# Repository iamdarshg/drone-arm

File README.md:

This is a codebase that is woring to create a hardware+software solution for dron control and management in a relatively modular manner. 
This is a codebase that is woring to create a hardware+software solution for dron control and management in a relatively modular manner.
This needs to be inherenly zero-trust, zero-fail and easy to analyse statically. The langauge of choice is C, with rust and python tooling accepted as well.Follow the 10 rules as set by nasa for code, the same should apply here due to the similar no-fail environment.
Currently, the main control board has been designed and the auxiallry field-oriented control esc needs to be designed.
Ideally, as much of this code as possible should be library free and written entirely from scratch. If any libraries are used beyond standard c libararies, they should all be stored within this folder, nowehere else.
Please add as much documentation as is needed, whenevr you refer to something just download and leave it in the docs folder. Please use the pico SDK exclusively as a library for C and/or write everything using reigster level functions.
Build will occur via Meson & Ninja. This means we will be compiling the whole thing using the arm toolchain, against the headers and flash tables and such from the SDK.
When debug is enabled in the meson build, we will output the assembly instead of the .uf2 file.

## Motor Platform (selected prototype baseline)

The ESC (Rev-B) is being optimized for the **Flycci FA4119 KV350** ([product page](https://robu.in/product/flycci-fpv-brushless-motors-fa4119-350kv/)). The current prototype decision, alternatives, cost model, proposed 550 Kv rewind, selected 8x4.5 propeller and mandatory validation gates are documented in [hardware/motor_release/FA4119_PROPULSION_DECISION.md](hardware/motor_release/FA4119_PROPULSION_DECISION.md).

- 12N14P outrunner (**7 pole pairs**), stator 41x19 mm, 280 g w/ cable
- Recommended 10S-12S LiPo, 13" prop, 80 A ESC class
- Measured (12S, HQ13x9-3 3-blade): 8.18 kg max thrust / 3.47 kW max @ 48 V, 74 A battery
- A rewind to **approximately 550 kV** is the experimental target if stock-motor dyno results justify it. The chosen Orange HD 8045 propeller has no verified manufacturer RPM rating in the repository, so the 550 Kv/12S combination requires closed-loop RPM limiting and guarded testing; it is not flight-released.

### eRPM headroom

eRPM = mech RPM x pole pairs (7). At 12S max (50.4 V):

| Winding | No-load RPM | No-load eRPM | Published or initially governed loaded eRPM |
|---|---|---|---|
| 350 kV (stock) | 17,640 | ~123 k | ~77-80 k with the manufacturer's 13-inch test prop |
| 550 kV (rewind) | 27,720 | ~194 k | initially <=91 k with the 8-inch prop (13,000 mechanical-rpm ceiling) |

**280 k eRPM check:** 280 k eRPM = 4.67 kHz electrical = 40,000 mechanical RPM at 7 pole pairs. This remains a possible future bare-rotor research point, not a propeller operating point. An 8-inch prop at 40,000 RPM has approximately 426 m/s rotational tip speed before pitch velocity and is unsuitable. The proposed 550 Kv winding reaches 194 k eRPM at fully charged 12S; initial propeller testing is capped at 13,000 mechanical RPM (91 k eRPM) pending a verified rating for the exact propeller.

## Build Instructions

This project uses Meson and Ninja for building.

### Prerequisites
- [ARM GNU Toolchain](https://developer.arm.com/Tools%20and%20Software/GNU%20Toolchain) (`arm-none-eabi-gcc`)
- [Meson](https://mesonbuild.com/)
- [Ninja](https://ninja-build.com/)
- Python 3

### Configuration
Create a build directory and configure the project:
```bash
meson setup build
```

To enable **Debug Mode** (includes assembly output and `-O0`):
```bash
meson setup build -Ddebug=enabled 
```

### Building
The documented firmware targets are currently blocked: the tracked checkout is
missing source and include paths required by `meson.build`, and the ARM GNU
cross compiler is not available in the build environment. Do not treat this
checkout as producing flight or ESC firmware. See the
[Issue #22 source and build audit](docs/engineering/FIRMWARE_SOURCE_AUDIT.md)
for the reproducible audit commands and recorded failures.

When the required source and toolchain are restored, the intended build command
is:
```bash
ninja -C build
```

### Testing
To build and run the unit tests:
```bash
meson test -C build
```
Current tests include:
- `test_main`: Scheduler and basic async operations.
- `test_clock_safety`: (New) Integrity protection for global clock state.
The main software will run as two non-synchronised loops- the sensor loop and the PWM loop. The one loop will run at the speed of the ESCs and will provide the best estimate for what the thrust should be at any given time to the ESCs, 60Hz if communicating via PWM and 1 kHz if communicating via SPI. This rate will be configurable. This loop may also be offloaded to the PIO modules in the future. The other loop is reponsible for sensor measuerment and fusion.

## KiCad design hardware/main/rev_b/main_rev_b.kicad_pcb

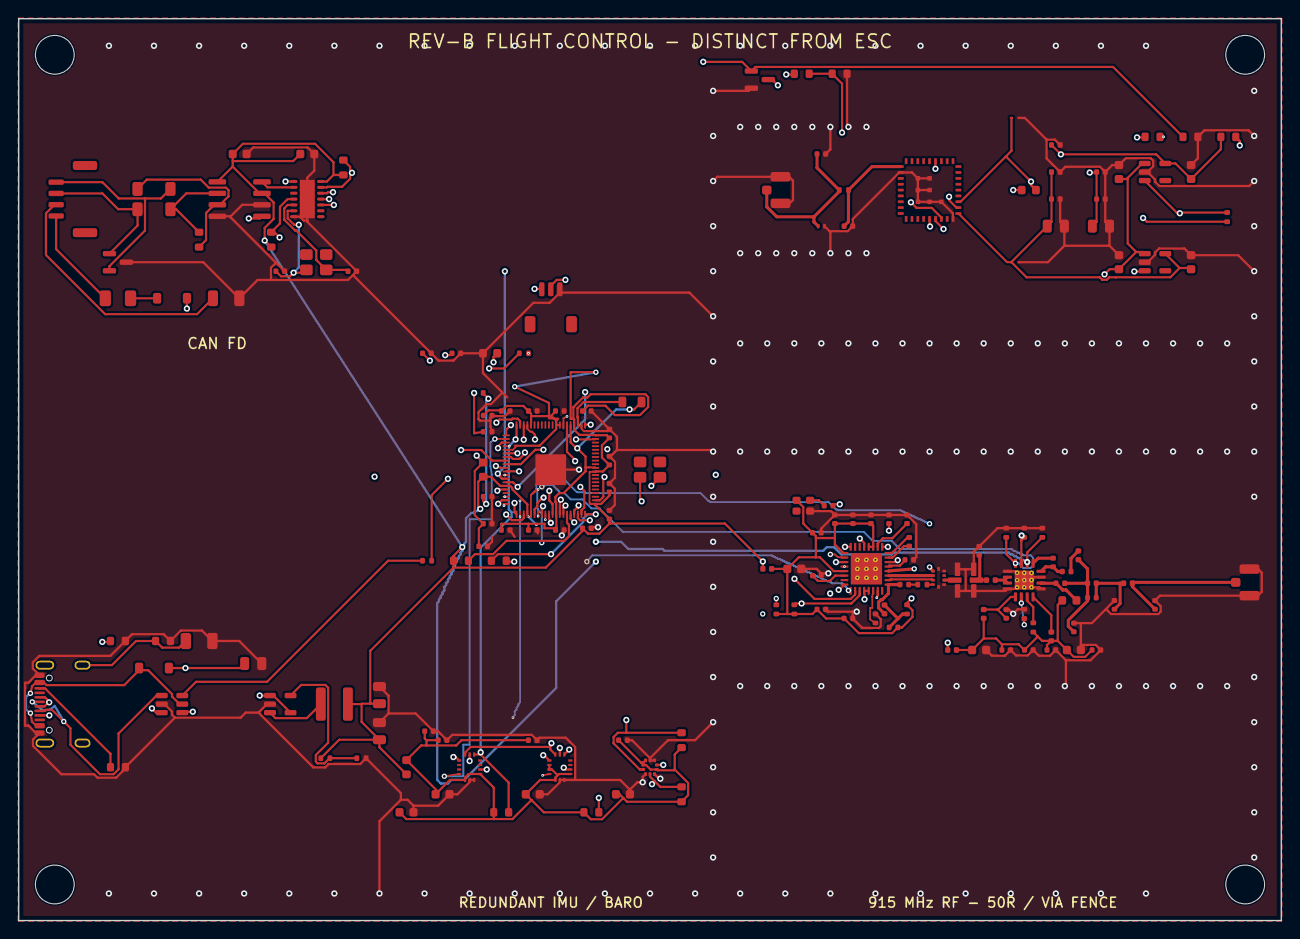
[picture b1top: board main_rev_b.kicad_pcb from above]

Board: 4 copper layers, 140.0 x 100.0 mm, 165 parts (0 on the bottom side), 111 nets.

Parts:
C1: 4.7u 10V; C_0805_2012Metric
C2, C6: 10u 10V; C_0805_2012Metric
C3, C4, C7, C8, C114: 1u; C_0603_1608Metric
C5: 4.7n 2kV; C_1206_3216Metric
C10, C11, C12, C13: 4.7u; C_0402_1005Metric
C20, C21, C86, C89, C120, C121: 15p C0G; C_0402_1005Metric
C30, C31, C32, C33, C34, C35, C36, C37, C38, C39, C40, C41, C42, C50, C52, C54, C56, C71, C75, C101, C115: 100n; C_0402_1005Metric
C51, C53, C55, C57, C100: 2.2u; C_0603_1608Metric
C70: 10u; C_0805_2012Metric
C72, C76, C85: 33p C0G; C_0402_1005Metric
C73: 1u; C_0402_1005Metric
C74: 4.7u; C_0805_2012Metric
C77, C78: DNP; C_0402_1005Metric
C80: 220n; C_0402_1005Metric
C81, C105: 10n; C_0402_1005Metric
C82, C83, C102, C103, C104: 47n; C_0402_1005Metric
C84: 22p C0G; C_0402_1005Metric
C87: 1.8n U2J; C_0402_1005Metric
C88: 0.8p C0G; C_0402_1005Metric
C90: 47p C0G; C_0402_1005Metric
C91: 3.3p C0G; C_0402_1005Metric
C92, C93: 12p C0G; C_0402_1005Metric
C94: 2.4p DNP; C_0402_1005Metric
C95: 7.5p C0G; C_0402_1005Metric
C96: 2.7p DNP; C_0402_1005Metric
C106: 100p; C_0402_1005Metric
C110: 10u; C_0603_1608Metric
C111: 27p; C_0402_1005Metric
C112: 47p; C_0402_1005Metric
C113: 1n; C_0402_1005Metric
C122, C123: 100n; C_0603_1608Metric
D1, D2: PMEG2010ER; D_SOD-123
D10: GREEN; LED_0603_1608Metric
D30: TPD1E0B04DPYR; Texas_DPY0002A_0.6x1mm_P0.65mm
D31, D32: ESD9B3.3ST5G; D_SOD-923
D50: PESD2CANFD24L-T; SOT-23
F1: PTC 0.75A; Fuse_1206_3216Metric
FB1, FB20, FB30: 600R@100MHz; L_0603_1608Metric
FL40: LFD21868MMF1D386
FL41: B39921B3588U410; RF_Filter_4Port
FL50: ACT45B-110-2P-TL003; L_CommonModeChoke_Coilank_ACM4532
H1, H2, H3, H4: M4; MountingHole_4.3mm_M4
J1: USB-C USB2; USB_C_Receptacle_GCT_USB4105-xx-A_16P_TopMnt_Horizontal
J2: ESC_CAN_POWER; JST_GH_SM04B-GHS-TB_1x04-1MP_P1.25mm_Horizontal
J10: SWD; JST_SH_SM03B-SRSS-TB_1x03-1MP_P1.00mm_Horizontal
J30: GNSS_UFL; U.FL_Hirose_U.FL-R-SMT-1_Vertical
J40: 915MHz_ANT; U.FL_Hirose_U.FL-R-SMT-1_Vertical
L1: 3.3u AOTA-B201610S3R3-101-T; L_0805_2012Metric
L2: 2.2u 3.5A; L_APV_ANR4018
L40: 1k@100MHz; L_0402_1005Metric
L41: 8.2n; L_0402_1005Metric
L42, L45: 10n; L_0402_1005Metric
L43: 1.5n; L_0402_1005Metric
L44: 15n; L_0402_1005Metric
L46: 22n; L_0603_1608Metric
L47: 7.5n; L_0402_1005Metric
L48: 2.9n; L_0402_1005Metric
L49: 9.1n; L_0402_1005Metric
Q30: 2N7002; SOT-23
R1, R2: 5.1k; R_0603_1608Metric
R3: 0 STAR; R_1206_3216Metric
R4: 33; R_0402_1005Metric
R5: 1M; R_0603_1608Metric
R6: 453k 1%; R_0402_1005Metric
R7: 100k 1%; R_0402_1005Metric
R8, R45, R46, R47: 100k; R_0402_1005Metric
R10, R11: 27; R_0402_1005Metric
R12, R22, R23, R34, R120, R121: 10k; R_0603_1608Metric
R13, R30: 1k; R_0603_1608Metric
R20, R21: 4.7k; R_0603_1608Metric
R31: 5.6k; R_0603_1608Metric
R32: 33; R_0603_1608Metric
R33: 100k; R_0603_1608Metric
R35: 0; R_0402_1005Metric
R40: 56k; R_0402_1005Metric
R41: 10; R_0402_1005Metric
R42: 0 (non-SigFox); R_0402_1005Metric
R43, R44: 10k; R_0402_1005Metric
R50: 3.3k; R_0402_1005Metric
R51: 47; R_0402_1005Metric
R122: 120 DNP; R_0603_1608Metric
U1: USBLC6-2SC6; SOT-23-6
U2: TLV62569DBVR; SOT-23-5
U3: TLV75528PDBVR; SOT-23-5
U4: TLV75533PDBVR; SOT-23-5
U10: RP2354B; QFN-80-1EP_10x10mm_P0.4mm_EP3.4x3.4mm
U20: ICM-42688-P; ICM42688P_LGA14
U21: LSM6DSO32TR; LSM6DSO32_LGA14
U22: LPS22DFTR; ST_HLGA-10_2x2mm_P0.5mm_LayoutBorder3x2y
U30: LG77LICMD; LG77L_LGA43
U40: CC1121RHBR; Texas_RHB0032E_VQFN-32-1EP_5x5mm_P0.5mm_EP3.45x3.45mm_Therm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
U41: CC1190RGVR; Texas_RGV0016A_VQFN-16-1EP_4x4mm_P0.65mm_EP2.1x2.1mm_Therma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
U50: TCAN3413DR; SOIC-8_3.9x4.9mm_P1.27mm
U51: MCP2518FD-H/QBB; DFN-14-1EP_3x4.5mm_P0.65mm_EP1.65x4.25mm
Y1: 12MHz ABM8-272-T3; Crystal_SMD_3225-4Pin_3.2x2.5mm
Y40: 32MHz NT2016SA-32M-TEE3017A; Oscillator_SMD_SiT_PQFN-4Pin_2.0x1.6mm
Y50: 40MHz ABM8G; Crystal_SMD_3225-4Pin_3.2x2.5mm

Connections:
/1V1: C11.1, C39.1, C40.1, C41.1, L1.2, R4.1, U10.10, U10.32, U10.51, U10.65
/2V8_GNSS: C4.1, C73.1, R34.1, U3.5, U30.20
/3V3: C2.1, C6.1, C10.1, C30.1, C31.1, C32.1, C33.1, C34.1, C35.1, C36.1, C37.1, C38.1, C122.1, C123.1, FB1.1, FB20.1, FB30.1, L2.2, L40.1, L45.1, R6.1, R8.1, R12.1, R120.1, R121.1, U10.5, U10.15, U10.24, U10.29, U10.41, U10.50, U10.60, U10.64, U10.68, U10.69, U10.76, U50.3, U50.5, U51.14
/3V3_ADC: C13.1, C42.1, FB1.2, U10.59
/3V3_GNSS: C8.1, C70.1, C71.1, C72.1, D31.1, U4.5, U30.19
/915 MHz RF/ANT_915: C96.1, J40.1, L49.2
/915 MHz RF/CC1121_RF: FL40.2, FL41.5
/915 MHz RF/CC1190_BIAS: R50.1, U41.14
/915 MHz RF/CC1190_VDD13: C89.1, L43.2, U41.13
/915 MHz RF/CC1190_VDD15: R51.2, U41.15
/915 MHz RF/CC1190_VDD16: L44.2, U41.16
/915 MHz RF/CC_DCPL: C80.1, U40.6
/915 MHz RF/CC_DCPL_PFD: C82.1, U40.26
/915 MHz RF/CC_DCPL_VCO: C81.1, U40.21
/915 MHz RF/CC_DCPL_XOSC: C83.1, U40.29
/915 MHz RF/CC_EXTCLK: C84.2, U40.32
/915 MHz RF/CC_LNA_N: FL40.6, U40.20
/915 MHz RF/CC_LNA_P: FL40.7, U40.19
/915 MHz RF/CC_LPF0: C87.1, U40.23
/915 MHz RF/CC_LPF1: C87.2, U40.24
/915 MHz RF/CC_PA: C86.1, L41.1, U40.17
/915 MHz RF/CC_PA_BIAS: C85.1, L41.2, R41.1
/915 MHz RF/CC_RBIAS: R40.1, U40.14
/915 MHz RF/CC_TRX_SW: FL40.8, U40.18
/915 MHz RF/CC_TXPA: FL40.9, R42.2
/915 MHz RF/CC_TX_PRE: C86.2, R42.1
/915 MHz RF/MATCH_A: C90.2, C91.1, C94.1, L47.1, L48.1
/915 MHz RF/MATCH_B: C94.2, C95.1, L48.2, L49.1
/915 MHz RF/RF_LNA_IN: C93.2, U41.5
/915 MHz RF/RF_PA_INOUT: L42.2, U41.10, U41.11
/915 MHz RF/RF_PA_OUT: C90.1, L46.2, U41.2
/915 MHz RF/RF_TR_SW: C92.2, C93.1, U41.4
/915 MHz RF/RX_COMBINE: C92.1, L47.2
/915 MHz RF/SAW_PA: C88.1, FL41.2, L42.1
/915 MHz RF/TCXO_RAW: C84.1, Y40.3
/915 MHz RF/VDD_CC112: C85.2, C100.1, C101.1, C102.1, C103.1, C104.1, C105.1, C106.1, L40.2, R41.2, R43.1, R44.1, U40.1, U40.5, U40.12, U40.13, U40.15, U40.22, U40.25, U40.27, U40.28, Y40.4
/915 MHz RF/VDD_CC119: C110.1, C111.1, C112.1, C113.1, C114.1, C115.1, L43.1, L44.1, L45.2, L46.1, R51.1
/BARO_DRDY: U10.9, U22.7
/BARO_SCL: R20.2, U10.7, U22.2
/BARO_SDA: R21.2, U10.8, U22.4
/CAN interface/U50_CANH: FL50.1, R122.1, U50.7
/CAN interface/U50_CANL: FL50.3, R122.2, U50.6
/CAN interface/U51_OSC1: C120.1, U51.6, Y50.1
/CAN interface/U51_OSC2: C121.1, U51.5, Y50.2
/CAN interface/U51_RXCAN: U50.4, U51.2
/CAN interface/U51_TXCAN: U50.1, U51.1
/CANH: D50.1, FL50.2, J2.3
/CANL: D50.2, FL50.4, J2.4
/CAN_5V: F1.1, J2.1
/CAN_GND: J2.2, R3.1
/CAN_INT: R121.2, U10.39, U51.4
/CAN_MISO: U10.37, U51.12
/CAN_MOSI: U10.36, U51.11
/CAN_SCK: U10.28, U51.10
/CAN_nCS: R120.2, U10.38, U51.13
/GND: C1.2, C2.2, C3.2, C4.2, C5.2, C6.2, C7.2, C8.2, C10.2, C11.2, C12.2, C13.2, C20.2, C21.2, C30.2, C31.2, C32.2, C33.2, C34.2, C35.2, C36.2, C37.2, C38.2, C39.2, C40.2, C41.2, C42.2, C50.2, C51.2, C52.2, C53.2, C54.2, C55.2, C56.2, C57.2, C70.2, C71.2, C72.2, C73.2, C74.2, C75.2, C76.2, C77.2, C78.2, C80.2, C81.2, C82.2, C83.2, C88.2, C89.2, C91.2, C95.2, C96.2, C100.2, C101.2, C102.2, C103.2, C104.2, C105.2, C106.2, C110.2, C111.2, C112.2, C113.2, C114.2, C115.2, C120.2, C121.2, C122.2, C123.2, D10.1, D30.2, D31.2, D32.2, D50.3, FL40.1, FL40.4, FL40.5, FL40.10, FL41.1, FL41.3, FL41.4, FL41.6, J1.A1, J1.A12, J1.B1, J1.B12, J10.3, J30.2, J40.2, Q30.2, R1.2, R2.2, R3.2, R5.2, R7.2, R31.2, R33.2, R40.2, R45.2, R46.2, R47.2, R50.2, U1.2, U2.2, U3.2, U4.2, U10.62, U10.81, U20.6, U20.7, U21.6, U21.7, U22.3, U22.5, U22.8, U22.9, U30.2, U30.18, U30.37, U30.38, U30.39, U30.40, U30.41, U30.42, U30.43, U40.33, U41.1, U41.3, U41.9, U41.12, U41.17, U50.2, U50.8, U51.7, U51.15, Y40.2
/GNSS/GNSS_RESET_OD: Q30.3, R34.2, U30.14
/GNSS/GNSS_RF_ANT: C77.1, D30.1, J30.1, R35.1
/GNSS/GNSS_RF_IN: C78.1, R35.2, U30.1
/GNSS/GNSS_UART_RX_2V8: R30.2, R31.1, U30.15
/GNSS/GNSS_UART_TX_2V8: R32.1, U30.16
/GNSS/GNSS_VBCKP: C74.1, C75.1, C76.1, D32.1, FB30.2, U30.21
/GNSS_PPS: U10.13, U30.31
/GNSS_PWR_EN: R8.2, U3.3, U4.3, U10.42
/GNSS_RESET_N: Q30.1, R33.1, U10.14
/GNSS_RX: R32.2, U10.12
/GNSS_TX: R30.1, U10.11
/HGM: R47.1, U10.27, U41.6
/ICM_INT1: U10.2, U20.4
/ICM_INT2: U10.3, U20.9
/ICM_nCS: R22.2, U10.80, U20.12
/LNA_EN: R46.1, U10.26, U41.7
/LSM_INT1: U10.4, U21.4
/LSM_INT2: U10.6, U21.9
/LSM_nCS: R23.2, U10.1, U21.12
/PA_EN: R45.1, U10.25, U41.8
/Power and USB/BUCK_FB: R6.2, R7.1, U2.5
/Power and USB/BUCK_SW: L2.1, U2.3
/Power and USB/CAN_5V_FUSED: D2.1, F1.2
/Power and USB/CHASSIS: C5.1, J1.S1, R5.1
/Power and USB/USB_CC1: J1.A5, R1.1
/Power and USB/USB_CC2: J1.B5, R2.1
/Power and USB/USB_DN_CONN: J1.A7, J1.B7, U1.1
/Power and USB/USB_DP_CONN: J1.A6, J1.B6, U1.3
/Power and USB/USB_VBUS: D1.1, J1.A4, J1.A9, J1.B4, J1.B9, U1.5
/RF_GPIO0: U10.21, U40.10
/RF_GPIO2: U10.22, U40.4
/RF_GPIO3: U10.23, U40.3
/RF_MISO: U10.18, U40.9
/RF_MOSI: U10.17, U40.7
/RF_RESET_N: R44.2, U10.20, U40.2
/RF_SCLK: U10.16, U40.8
/RF_nCS: R43.2, U10.19, U40.11
/RP2354B MCU/MAIN_LED_A: D10.2, R13.2
/RP2354B MCU/RUN: R12.2, U10.35
/RP2354B MCU/STATUS_LED: R13.1, U10.40
/RP2354B MCU/SWCLK: J10.1, U10.33
/RP2354B MCU/SWDIO: J10.2, U10.34
/RP2354B MCU/USB_DM_MCU: R11.2, U10.66
/RP2354B MCU/USB_DP_MCU: R10.2, U10.67
/RP2354B MCU/XIN: C20.1, U10.30, Y1.1
/RP2354B MCU/XOUT: C21.1, U10.31, Y1.2
/Redundant sensors/3V3_SENS: C50.1, C51.1, C52.1, C53.1, C54.1, C55.1, C56.1, C57.1, FB20.2, R20.1, R21.1, R22.1, R23.1, U20.5, U20.8, U21.2, U21.3, U21.5, U21.8, U22.1, U22.6, U22.10
/SENS_MISO: U10.79, U20.1, U21.1
/SENS_MOSI: U10.78, U20.14, U21.14
/SENS_SCLK: U10.77, U20.13, U21.13
/SYS_5V: C1.1, C3.1, C7.1, D1.2, D2.2, U2.1, U2.4, U3.1, U4.1
/USB_DM: R11.1, U1.6
/USB_DP: R10.1, U1.4
/VREG_AVDD: C12.1, R4.2, U10.61
/VREG_LX: L1.1, U10.63

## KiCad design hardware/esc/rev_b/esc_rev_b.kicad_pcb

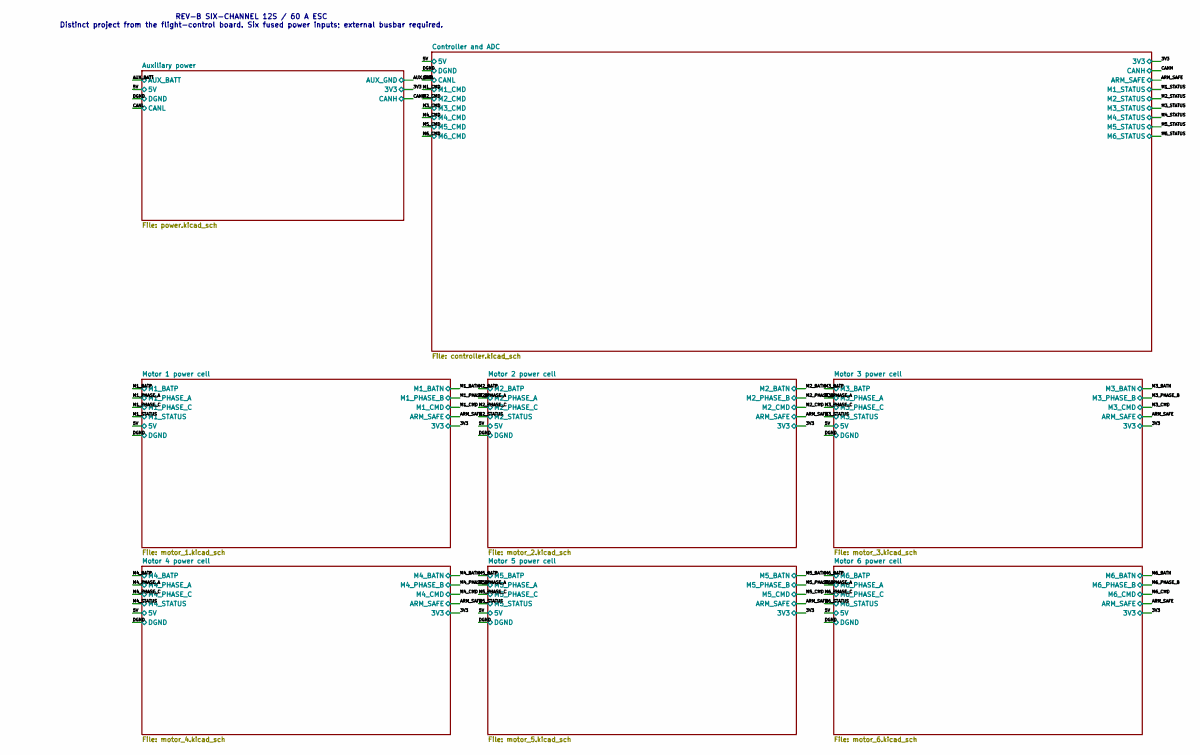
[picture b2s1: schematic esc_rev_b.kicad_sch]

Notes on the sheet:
REV-B SIX-CHANNEL 12S / 60 A ESC Distinct project from the flight-control board. Six fused power inputs; external busbar required.

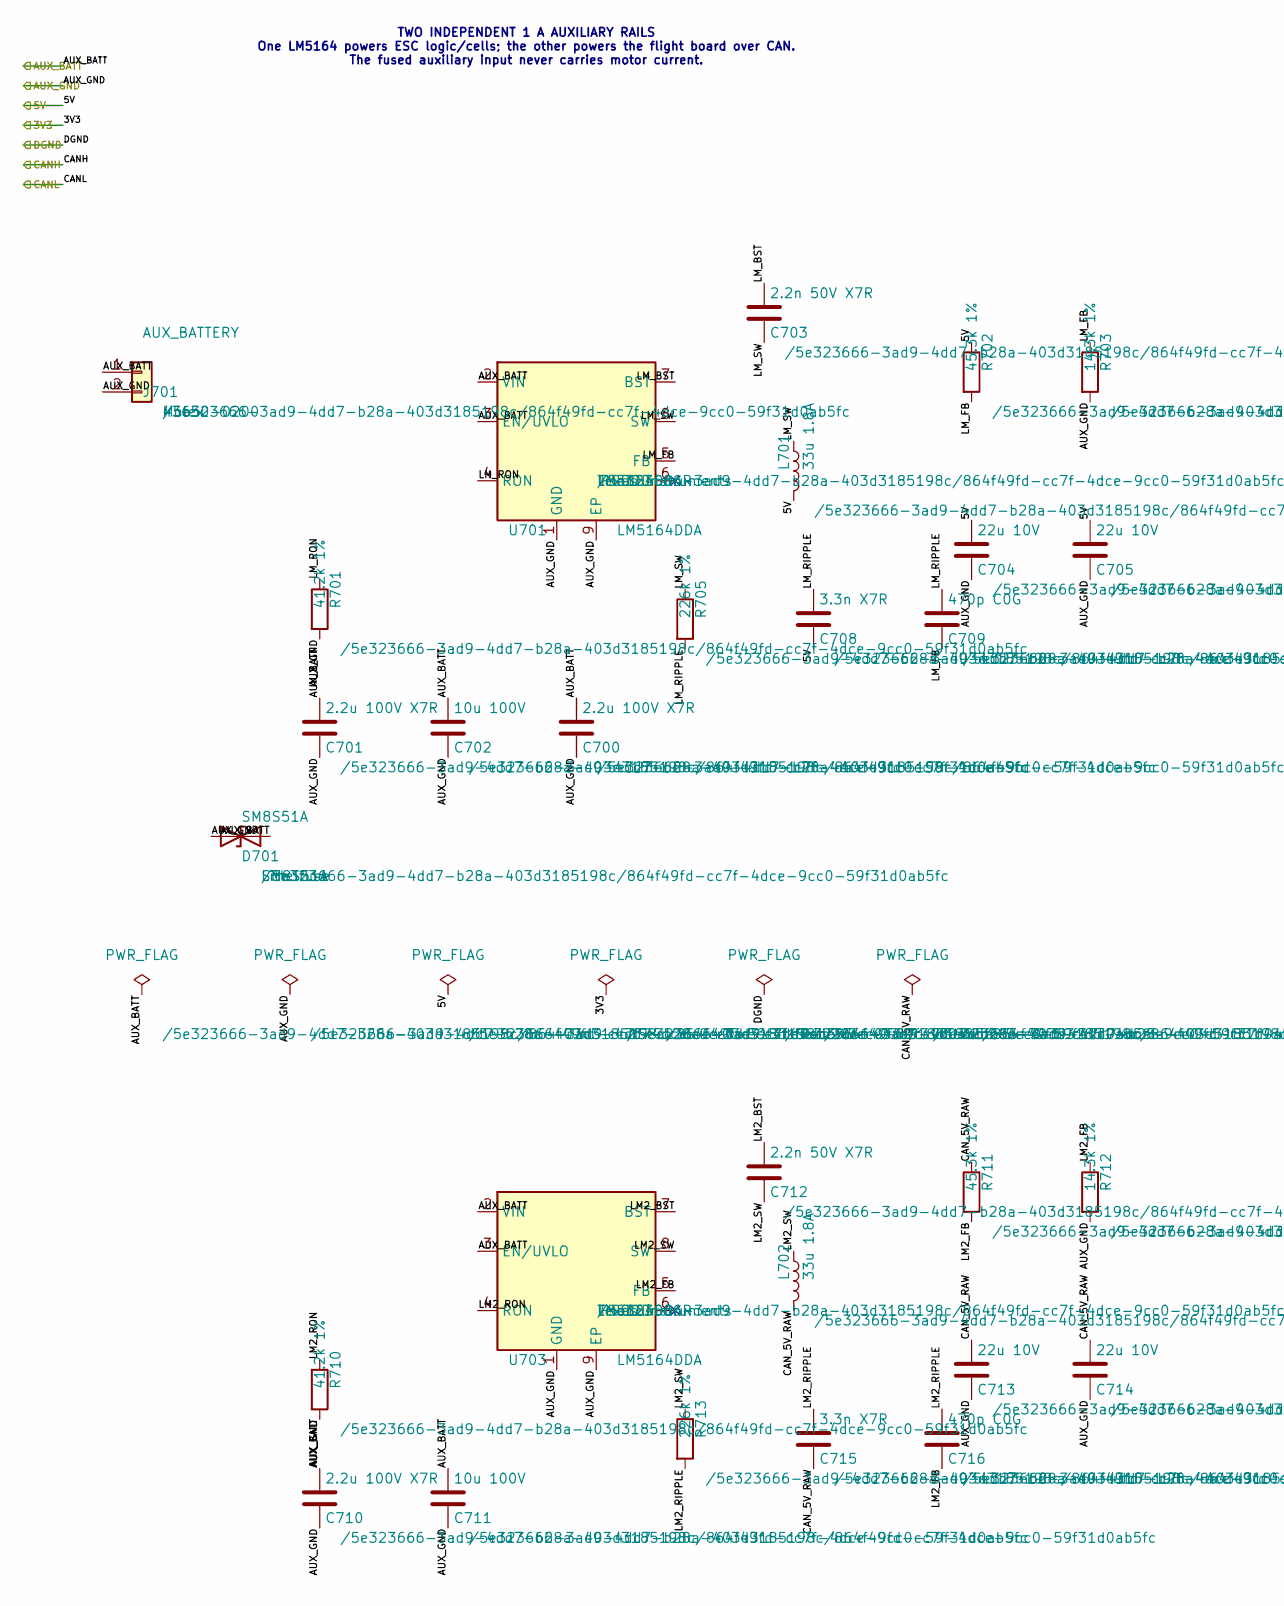
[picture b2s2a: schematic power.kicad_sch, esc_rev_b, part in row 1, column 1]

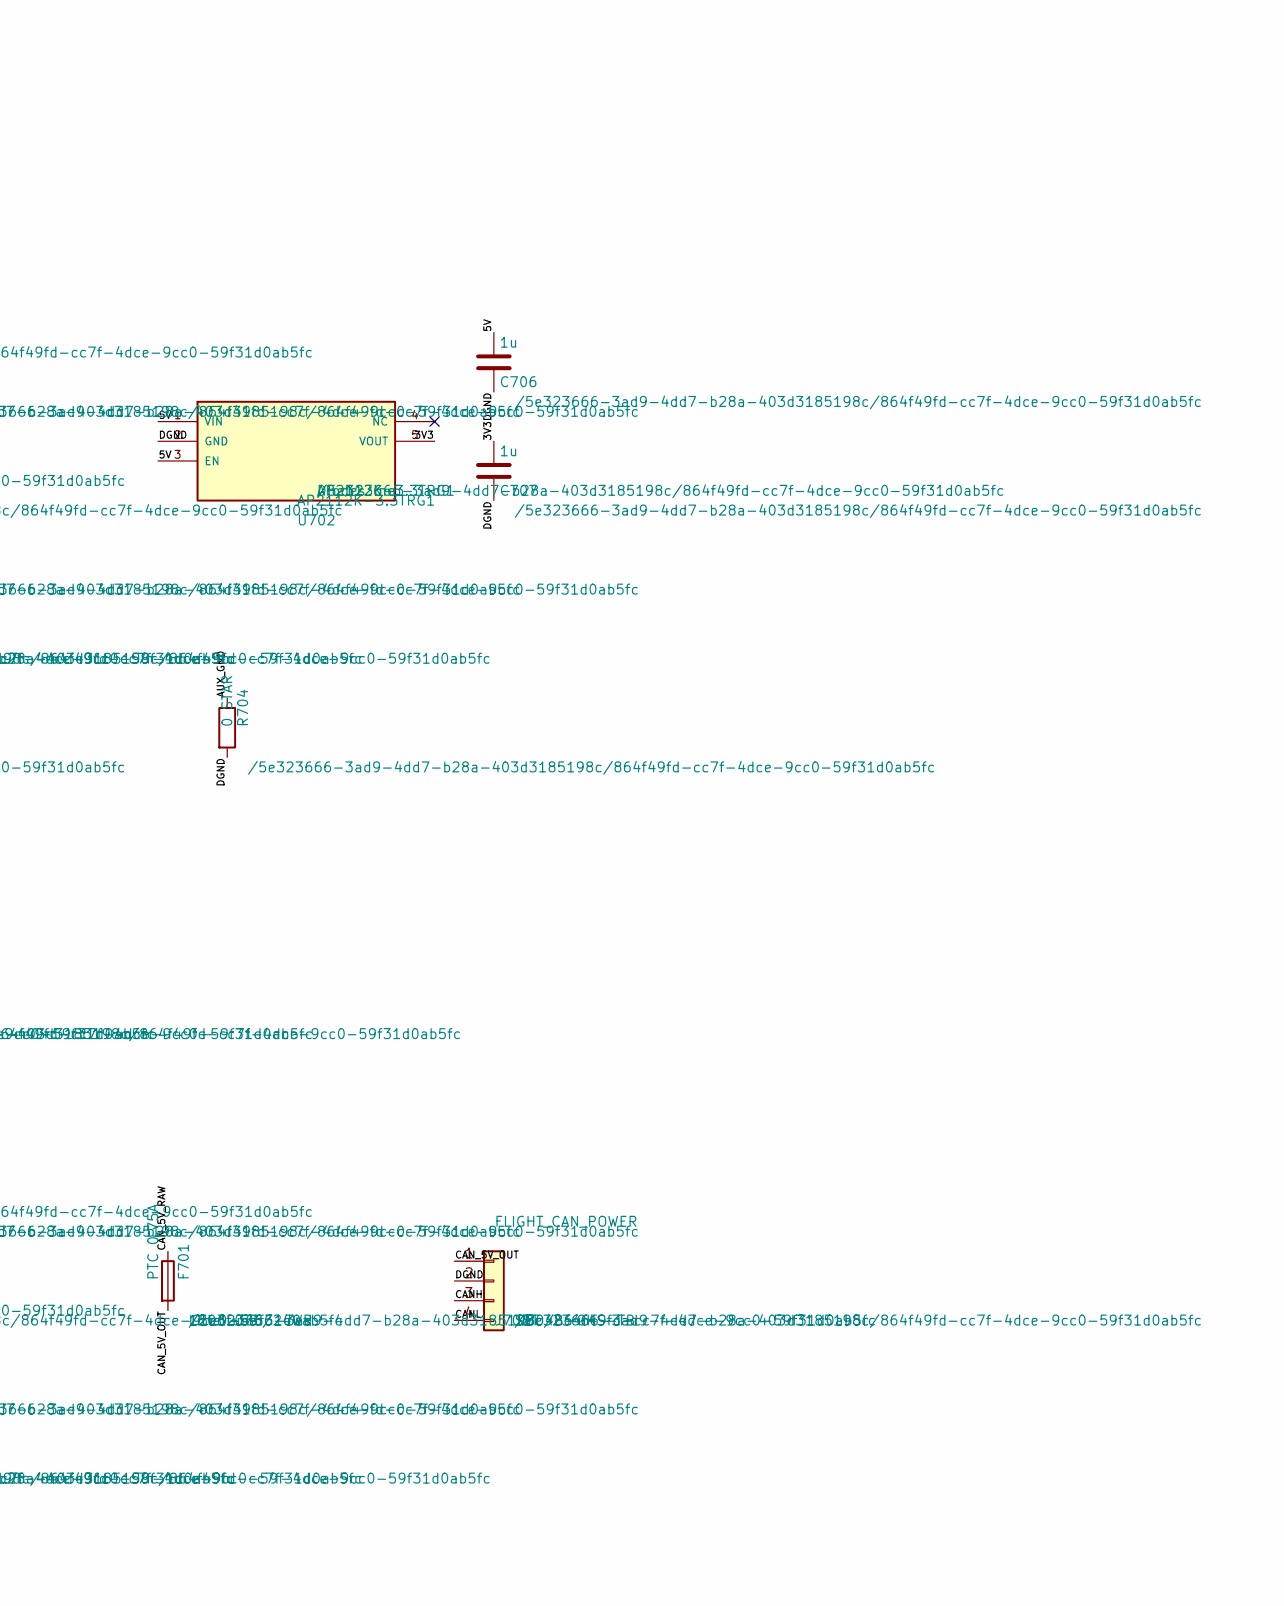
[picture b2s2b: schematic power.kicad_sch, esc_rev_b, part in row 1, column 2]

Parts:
C700, C701, C710: 2.2u 100V X7R; C_1210_3225Metric
C702, C711: 10u 100V; C_1210_3225Metric
C703, C712: 2.2n 50V X7R; C_0603_1608Metric
C704, C705, C713, C714: 22u 10V; C_1210_3225Metric
C706, C707: 1u; C_0603_1608Metric
C708, C715: 3.3n X7R; C_0603_1608Metric
C709, C716: 470p C0G; C_0603_1608Metric
D701: SM8S51A; DO-218AB_SM8S; MPN SM8S51A
F701: PTC 0.75A; Fuse_1206_3216Metric; MPN 1206L075/24WR
J701: AUX_BATTERY; Molex_Micro-Fit_3.0_43650-0200_1x02_P3.00mm_Horizontal; MPN 43650-0200
J702: FLIGHT_CAN_POWER; JST_GH_SM04B-GHS-TB_1x04-1MP_P1.25mm_Horizontal; MPN SM04B-GHS-TB
L701, L702: 33u 1.8A; L_Bourns_SRR1260
R701, R710: 41.2k 1%; R_0603_1608Metric
R702, R711: 45.3k 1%; R_0603_1608Metric
R703, R712: 14.3k 1%; R_0603_1608Metric
R704: 0 STAR; R_1206_3216Metric
R705, R713: 226k 1%; R_0603_1608Metric
U701, U703: LM5164DDA; HSOP-8-1EP_3.9x4.9mm_P1.27mm_EP2.41x3.1mm_ThermalVias; MPN LM5164DDAR
U702: AP2112K-3.3TRG1; SOT-23-5; MPN AP2112K-3.3TRG1

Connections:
/3V3: C707.1, U702.5 (VOUT); also elsewhere on the board
/5V: C704.1, C705.1, C706.1, C708.2, L701.2, R702.1, U702.1 (VIN), U702.3 (EN); also elsewhere on the board
/AUX_BATT: C700.1, C701.1, C702.1, C710.1, C711.1, D701.2 (A2), J701.1, U701.2 (VIN), U701.3 (EN/UVLO), U703.2 (VIN), U703.3 (EN/UVLO)
/AUX_GND: C700.2, C701.2, C702.2, C704.2, C705.2, C710.2, C711.2, C713.2, C714.2, D701.1 (A1), J701.2, R701.2, R703.2, R704.1, R710.2, R712.2, U701.1 (GND), U701.9 (EP), U703.1 (GND), U703.9 (EP)
/Auxiliary power/CAN_5V_OUT: F701.2, J702.1
/Auxiliary power/CAN_5V_RAW: C713.1, C714.1, C715.2, F701.1, L702.2, R711.1
/Auxiliary power/LM2_BST: C712.1, U703.7 (BST)
/Auxiliary power/LM2_FB: C716.2, R711.2, R712.1, U703.5 (FB)
/Auxiliary power/LM2_RIPPLE: C715.1, C716.1, R713.2
/Auxiliary power/LM2_RON: R710.1, U703.4 (RON)
/Auxiliary power/LM2_SW: C712.2, L702.1, R713.1, U703.8 (SW)
/Auxiliary power/LM_BST: C703.1, U701.7 (BST)
/Auxiliary power/LM_FB: C709.2, R702.2, R703.1, U701.5 (FB)
/Auxiliary power/LM_RIPPLE: C708.1, C709.1, R705.2
/Auxiliary power/LM_RON: R701.1, U701.4 (RON)
/Auxiliary power/LM_SW: C703.2, L701.1, R705.1, U701.8 (SW)
/CANH: J702.3; also elsewhere on the board
/CANL: J702.4; also elsewhere on the board
/DGND: C706.2, C707.2, J702.2, R704.2, U702.2 (GND); also elsewhere on the board

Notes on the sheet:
TWO INDEPENDENT 1 A AUXILIARY RAILS One LM5164 powers ESC logic/cells; the other powers the flight board over CAN. The fused auxiliary input never carries motor current.

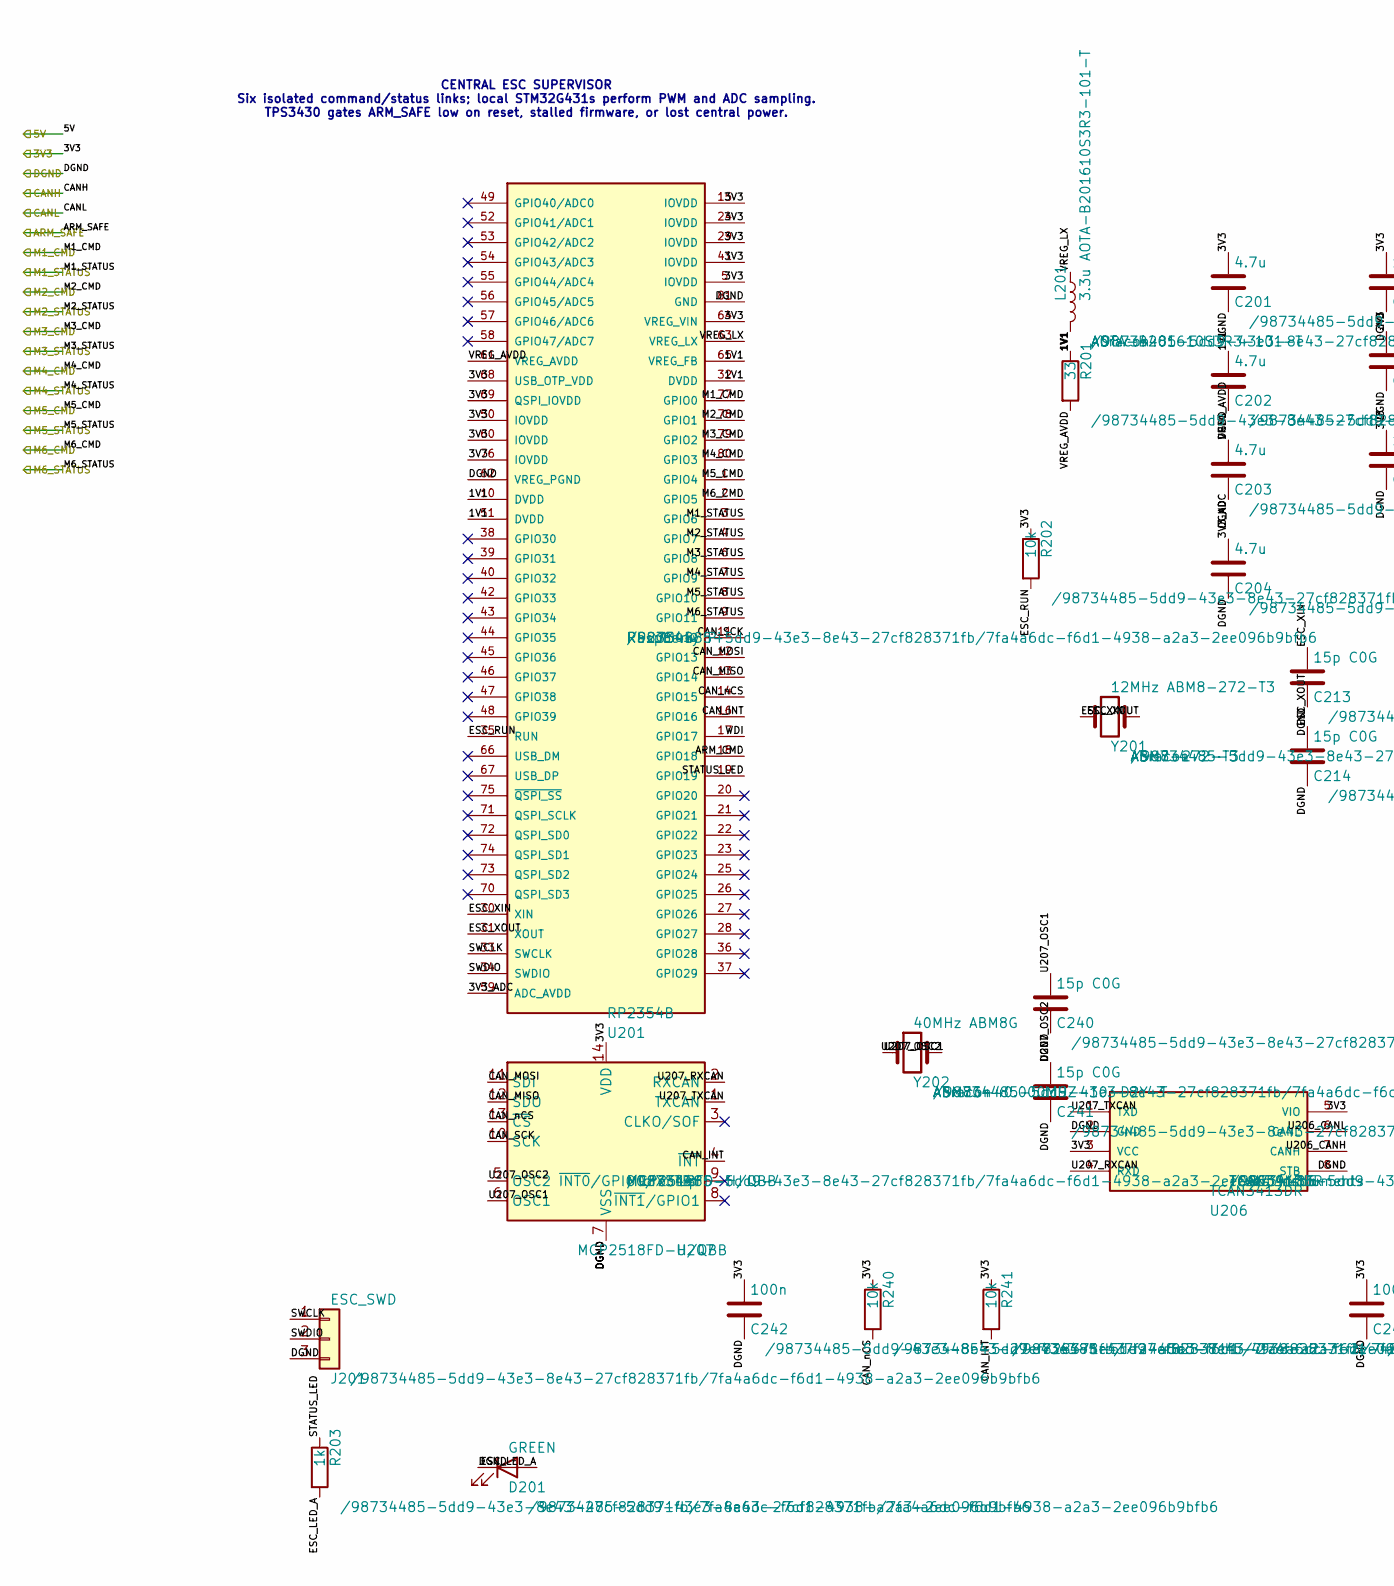
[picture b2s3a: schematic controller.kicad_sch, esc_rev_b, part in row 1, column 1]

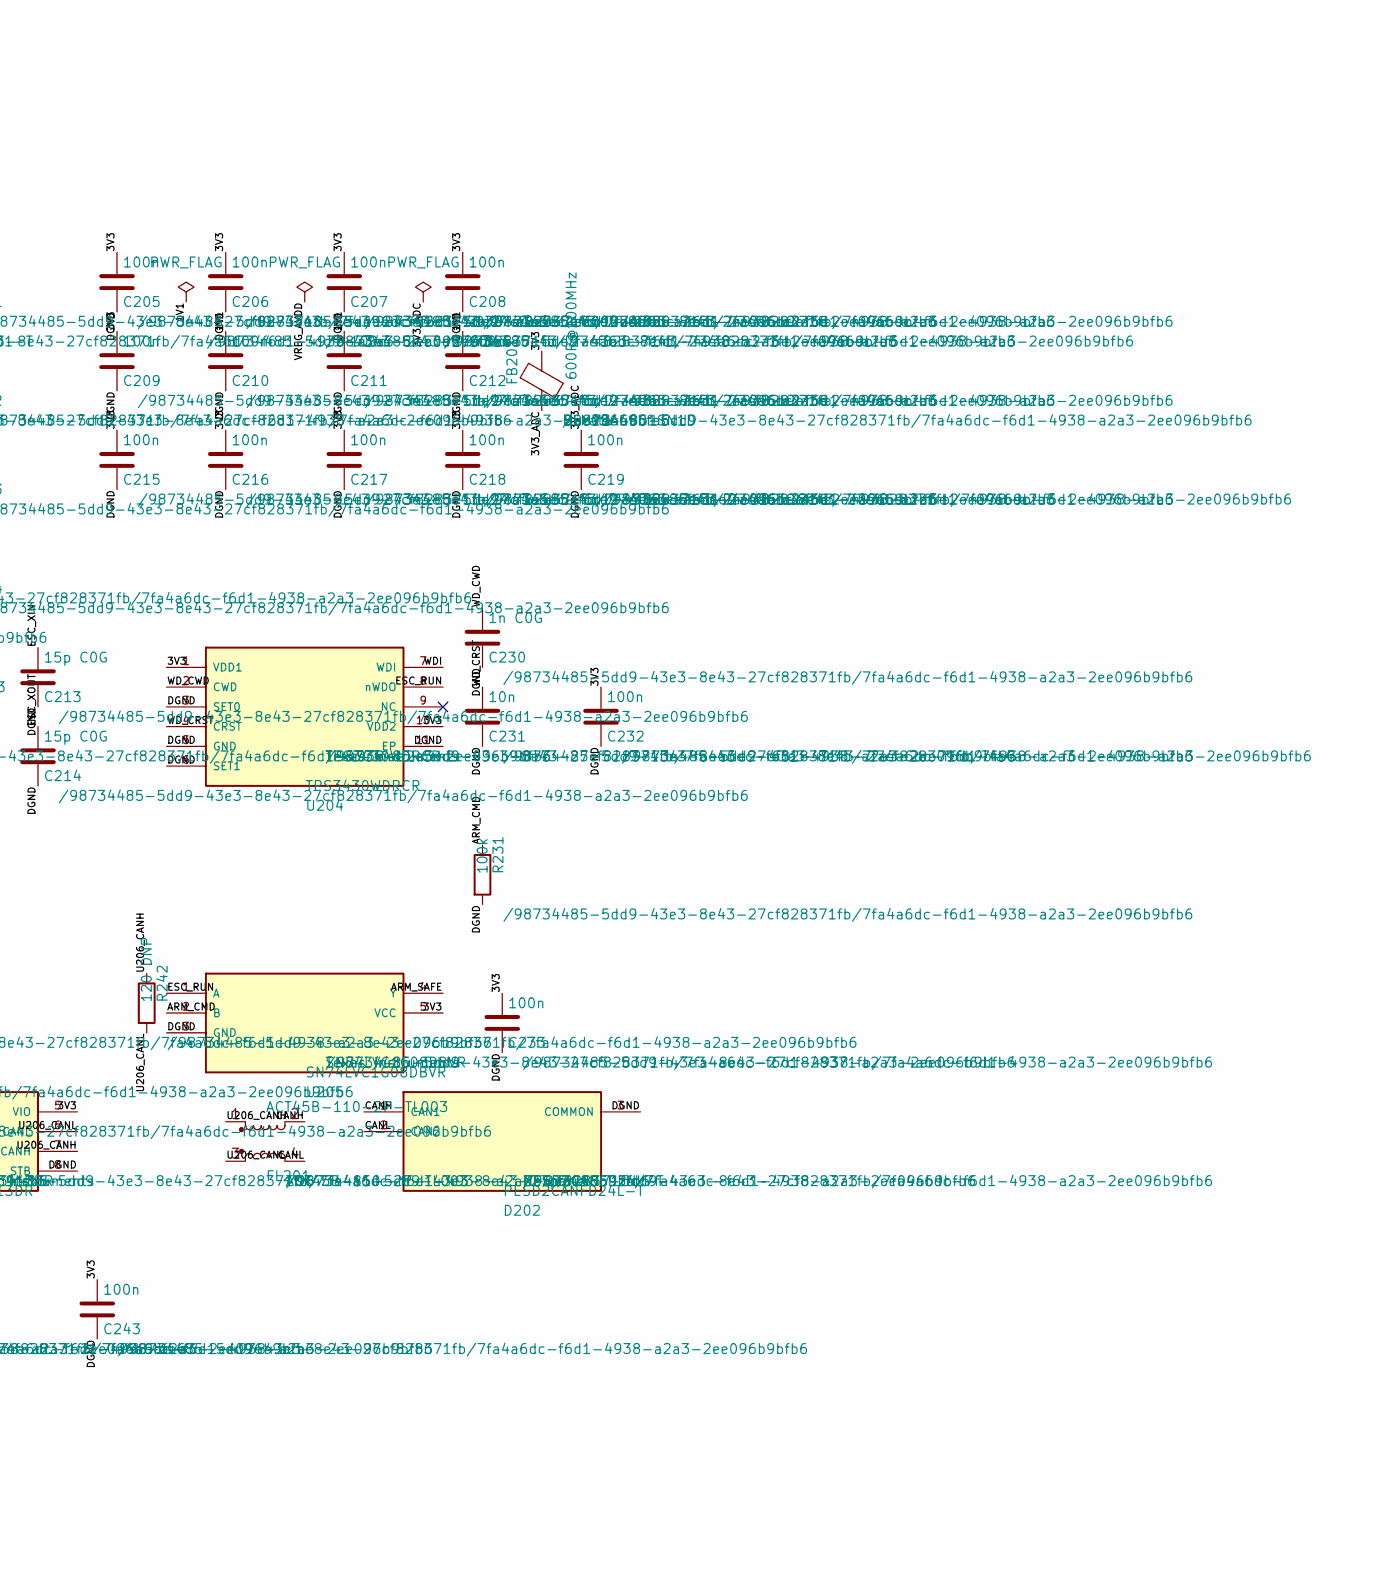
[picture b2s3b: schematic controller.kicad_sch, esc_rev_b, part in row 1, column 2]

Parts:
C201, C202, C203, C204: 4.7u; C_0402_1005Metric
C205, C206, C207, C208, C209, C210, C211, C212, C215, C216, C217, C218, C219: 100n; C_0402_1005Metric
C213, C214, C240, C241: 15p C0G; C_0402_1005Metric
C230: 1n C0G; C_0603_1608Metric
C231: 10n; C_0603_1608Metric
C232, C233, C242, C243: 100n; C_0603_1608Metric
D201: GREEN; LED_0603_1608Metric
D202: PESD2CANFD24L-T; SOT-23; MPN PESD2CANFD24L-T
FB201: 600R@100MHz; L_0603_1608Metric; MPN BLM18AG601SN1D
FL201: ACT45B-110-2P-TL003; L_CommonModeChoke_Coilank_ACM4532; MPN ACT45B-110-2P-TL003
J201: ESC_SWD; JST_SH_SM03B-SRSS-TB_1x03-1MP_P1.00mm_Horizontal
L201: 3.3u AOTA-B201610S3R3-101-T; L_0805_2012Metric; MPN AOTA-B201610S3R3-101-T
R201: 33; R_0402_1005Metric
R202, R240, R241: 10k; R_0603_1608Metric
R203: 1k; R_0603_1608Metric
R231: 100k; R_0603_1608Metric
R242: 120 DNP; R_0603_1608Metric
U201: RP2354B; QFN-80-1EP_10x10mm_P0.4mm_EP3.4x3.4mm; MPN RP2354B
U204: TPS3430WDRCR; TPS3430_WSON10_EP; MPN TPS3430WDRCR
U205: SN74LVC1G08DBVR; SOT-23-5; MPN SN74LVC1G08DBVR
U206: TCAN3413DR; SOIC-8_3.9x4.9mm_P1.27mm; MPN TCAN3413DR
U207: MCP2518FD-H/QBB; DFN-14-1EP_3x4.5mm_P0.65mm_EP1.65x4.25mm; MPN MCP2518FD-H/QBB
Y201: 12MHz ABM8-272-T3; Crystal_SMD_3225-4Pin_3.2x2.5mm; MPN ABM8-272-T3
Y202: 40MHz ABM8G; Crystal_SMD_3225-4Pin_3.2x2.5mm; MPN ABM8G-40.000MHZ-10-D2Y-T

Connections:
/3V3: C201.1, C205.1, C206.1, C207.1, C208.1, C209.1, C215.1, C216.1, C217.1, C218.1, C232.1, C233.1, C242.1, C243.1, FB201.1, R202.1, R240.1, R241.1, U201.5 (IOVDD), U201.15 (IOVDD), U201.24 (IOVDD), U201.29 (IOVDD), U201.41 (IOVDD), U201.50 (IOVDD), U201.60 (IOVDD), U201.64 (VREG_VIN), U201.68 (USB_OTP_VDD), U201.69 (QSPI_IOVDD), U201.76 (IOVDD), U204.1 (VDD1), U204.10 (VDD2), U205.5 (VCC), U206.3 (VCC), U206.5 (VIO), U207.14 (VDD); also elsewhere on the board
/ARM_SAFE: U205.4 (Y); also elsewhere on the board
/CANH: D202.1 (CAN1), FL201.2; also elsewhere on the board
/CANL: D202.2 (CAN2), FL201.4; also elsewhere on the board
/Controller and ADC/1V1: C202.1, C210.1, C211.1, C212.1, L201.2, R201.1, U201.10 (DVDD), U201.32 (DVDD), U201.51 (DVDD), U201.65 (VREG_FB)
/Controller and ADC/3V3_ADC: C204.1, C219.1, FB201.2, U201.59 (ADC_AVDD)
/Controller and ADC/ARM_CMD: R231.1, U201.18 (GPIO18), U205.2 (B)
/Controller and ADC/CAN_INT: R241.2, U201.16 (GPIO16), U207.4 (~INT)
/Controller and ADC/CAN_MISO: U201.13 (GPIO14), U207.12 (SDO)
/Controller and ADC/CAN_MOSI: U201.12 (GPIO13), U207.11 (SDI)
/Controller and ADC/CAN_SCK: U201.11 (GPIO12), U207.10 (SCK)
/Controller and ADC/CAN_nCS: R240.2, U201.14 (GPIO15), U207.13 (~CS)
/Controller and ADC/CTRL_USB_DM_MCU: U201.66 (USB_DM); also elsewhere on the board
/Controller and ADC/CTRL_USB_DP_MCU: U201.67 (USB_DP); also elsewhere on the board
/Controller and ADC/CTRL_USB_VBUS_SENSE: U201.20 (GPIO20); also elsewhere on the board
/Controller and ADC/ESC_LED_A: D201.2 (A), R203.2
/Controller and ADC/ESC_RUN: R202.2, U201.35 (RUN), U204.8 (nWDO), U205.1 (A)
/Controller and ADC/ESC_XIN: C213.1, U201.30 (XIN), Y201.1
/Controller and ADC/ESC_XOUT: C214.1, U201.31 (XOUT), Y201.2
/Controller and ADC/STATUS_LED: R203.1, U201.19 (GPIO19)
/Controller and ADC/SWCLK: J201.1, U201.33 (SWCLK)
/Controller and ADC/SWDIO: J201.2, U201.34 (SWDIO)
/Controller and ADC/U206_CANH: FL201.1, R242.1, U206.7 (CANH)
/Controller and ADC/U206_CANL: FL201.3, R242.2, U206.6 (CANL)
/Controller and ADC/U207_OSC1: C240.1, U207.6 (OSC1), Y202.1
/Controller and ADC/U207_OSC2: C241.1, U207.5 (OSC2), Y202.2
/Controller and ADC/U207_RXCAN: U206.4 (RXD), U207.2 (RXCAN)
/Controller and ADC/U207_TXCAN: U206.1 (TXD), U207.1 (TXCAN)
/Controller and ADC/VREG_AVDD: C203.1, R201.2, U201.61 (VREG_AVDD)
/Controller and ADC/VREG_LX: L201.1, U201.63 (VREG_LX)
/Controller and ADC/WDI: U201.17 (GPIO17), U204.7 (WDI)
/Controller and ADC/WD_CRST: C231.1, U204.4 (CRST)
/Controller and ADC/WD_CWD: C230.1, U204.2 (CWD)
/DGND: C201.2, C202.2, C203.2, C204.2, C205.2, C206.2, C207.2, C208.2, C209.2, C210.2, C211.2, C212.2, C213.2, C214.2, C215.2, C216.2, C217.2, C218.2, C219.2, C230.2, C231.2, C232.2, C233.2, C240.2, C241.2, C242.2, C243.2, D201.1 (K), D202.3 (COMMON), J201.3, R231.2, U201.62 (VREG_PGND), U201.81 (GND), U204.3 (SET0), U204.5 (GND), U204.6 (SET1), U204.11 (EP), U205.3 (GND), U206.2 (GND), U206.8 (STB), U207.7 (VSS), U207.15 (VSS); also elsewhere on the board
/M1_CMD: U201.77 (GPIO0); also elsewhere on the board
/M1_STATUS: U201.3 (GPIO6); also elsewhere on the board
/M2_CMD: U201.78 (GPIO1); also elsewhere on the board
/M2_STATUS: U201.4 (GPIO7); also elsewhere on the board
/M3_CMD: U201.79 (GPIO2); also elsewhere on the board
/M3_STATUS: U201.6 (GPIO8); also elsewhere on the board
/M4_CMD: U201.80 (GPIO3); also elsewhere on the board
/M4_STATUS: U201.7 (GPIO9); also elsewhere on the board
/M5_CMD: U201.1 (GPIO4); also elsewhere on the board
/M5_STATUS: U201.8 (GPIO10); also elsewhere on the board
/M6_CMD: U201.2 (GPIO5); also elsewhere on the board
/M6_STATUS: U201.9 (GPIO11); also elsewhere on the board

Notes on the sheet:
CENTRAL ESC SUPERVISOR Six isolated command/status links; local STM32G431s perform PWM and ADC sampling. TPS3430 gates ARM_SAFE low on reset, stalled firmware, or lost central power.
